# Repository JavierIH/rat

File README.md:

# RAT

Maze-solver mobile robot.

The code is being developed in [rat_sw](https://github.com/JavierIH/rat_sw)

NOTE: This project is actually under deep development, but contributions and reviews are welcomed :)

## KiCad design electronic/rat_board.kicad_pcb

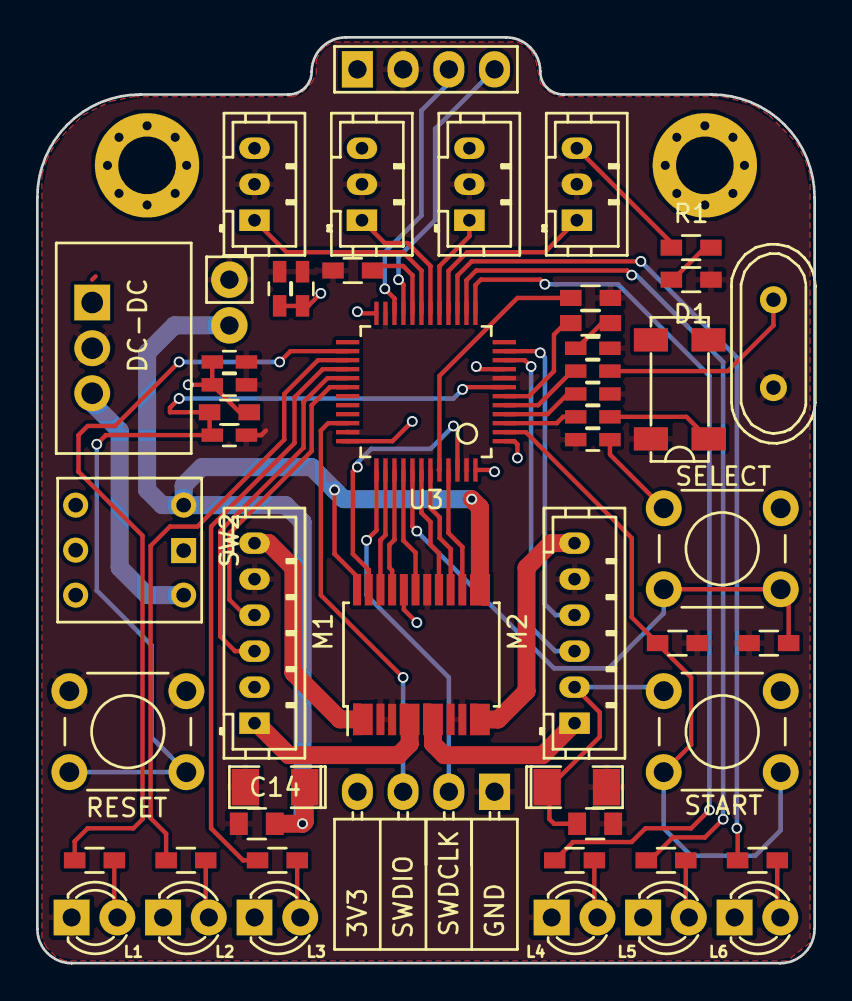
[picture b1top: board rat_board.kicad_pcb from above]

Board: 2 copper layers, 43.2 x 51.4 mm, 21 parts (0 on the bottom side), 15 nets.

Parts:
C14: 10uF; SMD-1206_Pol
D1: LED_Power; R_0603_HandSoldering
DC-DC: CONN_01X02; Socket_Strip_Straight_1x02
L1: LED_0; LED-3MM
L2: LED_1; LED-3MM
L3: LED_2; LED-3MM
L4: LED_3; LED-3MM
L5: LED_4; LED-3MM
L6: LED_5; LED-3MM
M1: LEFT_MOTOR; JST_PH_B6B-PH-K_06x2.00mm_Straight
M2: RIGHT_MOTOR; JST_PH_B6B-PH-K_06x2.00mm_Straight
R1: 100; R_0603_HandSoldering
RESET: SW_PUSH_SMALL_H; SW_PUSH_6mm
S1: FRONT_LEFT_IR; JST_PH_B3B-PH-K_03x2.00mm_Straight
S2: SIDE_LEFT_IR; JST_PH_B3B-PH-K_03x2.00mm_Straight
S3: SIDE_RIGHT_IR; JST_PH_B3B-PH-K_03x2.00mm_Straight
S4: FRONT_RIGHT_IR; JST_PH_B3B-PH-K_03x2.00mm_Straight
SELECT: SELECT_BUTTON; SW_PUSH_6mm
START: START_BUTTON; SW_PUSH_6mm
SW2: SWITCH_INV; SW_PUSH_x2
U3: STM32F103C8T6; LQFP-48_7x7mm_Pitch0.5mm

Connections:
+3V3: M1.2, M2.2, R1.1, S1.3, S2.3, S3.3, S4.3, SELECT.1, START.1, U3.1, U3.9, U3.24, U3.36, U3.48
+BATT: C14.1, DC-DC.1, SW2.3
/ENC1A: M1.3, U3.29
/ENC1B: M1.4, U3.30
/ENC2A: M2.3, U3.10
/ENC2B: M2.4, U3.11
/IR1: S1.1, U3.19
/IR2: S2.1, U3.18
/IR3: S3.1, U3.17
/IR4: S4.1, U3.16
/RESET: RESET.2, U3.7
/UB_SELECT: SELECT.2, U3.41
/UB_START: START.2, U3.2
GND: C14.2, D1.1, DC-DC.2, L1.1, L2.1, L3.1, L4.1, L5.1, L6.1, M1.5, M2.5, RESET.1, S1.2, S2.2, S3.2, S4.2, U3.8, U3.23, U3.35, U3.47
unnamed: D1.2, R1.2

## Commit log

2016-12-02 3D model under development
2016-12-03 minimal proof of concept code
2016-12-09 updated design
2016-12-12 added a battery support
2016-12-16 modelos de ruedas scaleauto
2016-12-25 Updated battery room
2016-12-27 redesigned batery room
2016-12-29 updated body
2016-12-30 room for components on body
2016-12-30 holes for body support bolts
2016-12-31 first commit of 2017 :D
2017-01-01 room for control leds and buttons
2017-01-01 support for lateral IR sensors
2017-01-02 updated 3d design with user interface components
2017-01-11 modified body supports
2017-01-12 beta stls for some printable parts
2017-01-19 minimal changes on freecad model
2017-01-19 proof of concept of peripherals
2017-01-21 added schematic for pcb design
2017-01-22 updates in pcb
2017-01-23 routing...
2017-01-29 updated pcb
2017-01-30 finished pcb
2017-01-30 added graphics on PCB
2017-02-02 proof of concept with IR sensors
2017-02-02 logos and filled zones
2017-02-02 added an additional uart connector
2017-02-11 small update
2017-02-11 smaller pushbutton on pcb
2017-07-25 added holes
2017-08-19 reallocate code to rat_sw repository
2017-08-23 modified chassis and baterry support
2017-08-23 component values on board
2017-08-26 added hole for bluetooth connection
